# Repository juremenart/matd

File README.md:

# 8x8 Acoustic levitator

Videos of prototype (2 x 8x8 boards with standing wave, done with data from this repo):

https://www.youtube.com/shorts/MVx3mwE5fvo

https://www.youtube.com/shorts/kOz_UAl6hNY

Levitation of 4 particles:

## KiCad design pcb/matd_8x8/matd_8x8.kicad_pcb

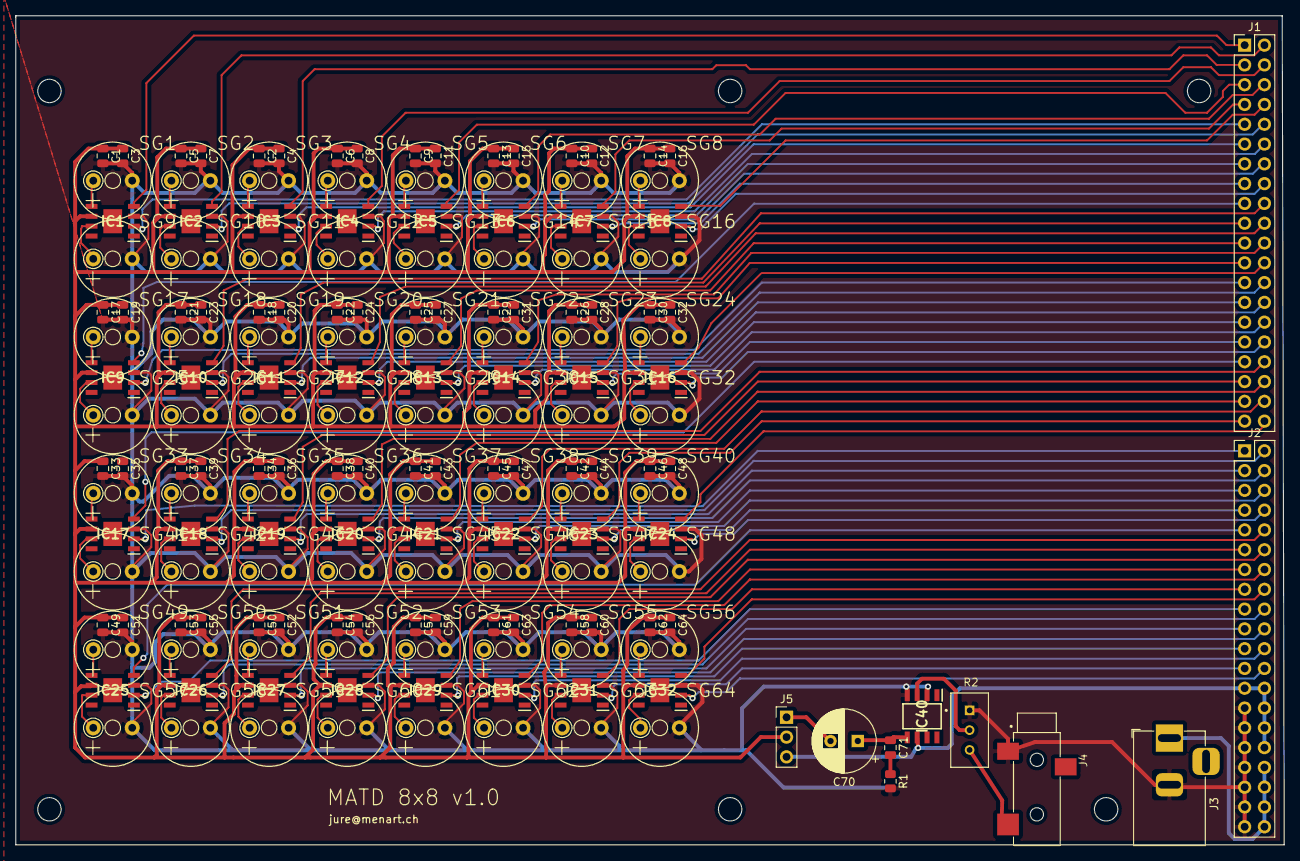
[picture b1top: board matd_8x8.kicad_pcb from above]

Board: 2 copper layers, 162.8 x 106.4 mm, 170 parts (0 on the bottom side), 137 nets.

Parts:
C1, C3, C5, C7, C9, C11, C13, C15, C17, C19, C21, C23, C25, C27, C29, C31, C33, C35, C37, C39, C41, C43, C45, C47, C49, C51, C53, C55, C57, C59, C61, C63: 4u7F; C_0805_2012Metric
C2, C4, C6, C8, C10, C12, C14, C16, C18, C20, C22, C24, C26, C28, C30, C32, C34, C36, C38, C40, C42, C44, C46, C48, C50, C52, C54, C56, C58, C60, C62, C64: 0u1F; C_0805_2012Metric
C70: 270uF; CP_Radial_D8.0mm_P3.50mm
C71: 0.05uF; C_0805_2012Metric
IC1, IC2, IC3, IC4, IC5, IC6, IC7, IC8, IC9, IC10, IC11, IC12, IC13, IC14, IC15, IC16, IC17, IC18, IC19, IC20, IC21, IC22, IC23, IC24, IC25, IC26, IC27, IC28, IC29, IC30, IC31, IC32: TC4427AEOA; SOIC127P602X168-9N
IC40: LM386M-1_NOPB; SOIC127P600X175-8N
J1, J2: Conn_02x20_Odd_Even; PinHeader_2x20_P2.54mm_Vertical
J3: Barrel_Jack; BarrelJack_Horizontal
J4: SJ-3523-SMT-TR; CUI_SJ-3523-SMT-TR
J5: Conn_01x03_Male; PinHeader_1x03_P2.54mm_Vertical
R1: 10; R_0805_2012Metric
R2: 3296W-1-103LF; TRIM_3296W-1-103LF
SG1, SG2, SG3, SG4, SG5, SG6, SG7, SG8, SG9, SG10, SG11, SG12, SG13, SG14, SG15, SG16, SG17, SG18, SG19, SG20, SG21, SG22, SG23, SG24, SG25, SG26, SG27, SG28, SG29, SG30, SG31, SG32, SG33, SG34, SG35, SG36, SG37, SG38, SG39, SG40, SG41, SG42, SG43, SG44, SG45, SG46, SG47, SG48, SG49, SG50, SG51, SG52, SG53, SG54, SG55, SG56, SG57, SG58, SG59, SG60, SG61, SG62, SG63, SG64: BMT1205XH7.5

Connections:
/SG1_SG16/SG1_IN: IC1.4, J1.1
/SG1_SG16/SG2_IN: IC2.4, J1.2
/SG1_SG16/SG3_IN: IC3.4, J1.3
/SG1_SG16/SG4_IN: IC4.4, J1.4
/SG1_SG16/SG5_IN: IC5.4, J1.5
/SG1_SG16/SG6_IN: IC6.4, J1.6
/SG1_SG16/SG7_IN: IC7.4, J1.7
/SG1_SG16/SG8_IN: IC8.4, J1.8
/SG1_SG16/SG9_IN: IC1.2, J1.9
/SG1_SG16/SG10_IN: IC2.2, J1.10
/SG1_SG16/SG11_IN: IC3.2, J1.11
/SG1_SG16/SG12_IN: IC4.2, J1.12
/SG1_SG16/SG13_IN: IC5.2, J1.13
/SG1_SG16/SG14_IN: IC6.2, J1.14
/SG1_SG16/SG15_IN: IC7.2, J1.15
/SG1_SG16/SG16_IN: IC8.2, J1.16
/SG17_SG32/SG17_IN: IC9.4, J1.17
/SG17_SG32/SG18_IN: IC10.4, J1.18
/SG17_SG32/SG19_IN: IC11.4, J1.19
/SG17_SG32/SG20_IN: IC12.4, J1.20
/SG17_SG32/SG21_IN: IC13.4, J1.21
/SG17_SG32/SG22_IN: IC14.4, J1.22
/SG17_SG32/SG23_IN: IC15.4, J1.23
/SG17_SG32/SG24_IN: IC16.4, J1.24
/SG17_SG32/SG25_IN: IC9.2, J1.25
/SG17_SG32/SG26_IN: IC10.2, J1.26
/SG17_SG32/SG27_IN: IC11.2, J1.27
/SG17_SG32/SG28_IN: IC12.2, J1.28
/SG17_SG32/SG29_IN: IC13.2, J1.29
/SG17_SG32/SG30_IN: IC14.2, J1.30
/SG17_SG32/SG31_IN: IC15.2, J1.31
/SG17_SG32/SG32_IN: IC16.2, J1.32
/SG17_SG32/VCC: C1.1, C2.1, C3.1, C4.1, C5.1, C6.1, C7.1, C8.1, C9.1, C10.1, C11.1, C12.1, C13.1, C14.1, C15.1, C16.1, C17.1, C18.1, C19.1, C20.1, C21.1, C22.1, C23.1, C24.1, C25.1, C26.1, C27.1, C28.1, C29.1, C30.1, C31.1, C32.1, C33.1, C34.1, C35.1, C36.1, C37.1, C38.1, C39.1, C40.1, C41.1, C42.1, C43.1, C44.1, C45.1, C46.1, C47.1, C48.1, C49.1, C50.1, C51.1, C52.1, C53.1, C54.1, C55.1, C56.1, C57.1, C58.1, C59.1, C60.1, C61.1, C62.1, C63.1, C64.1, IC1.6, IC2.6, IC3.6, IC4.6, IC5.6, IC6.6, IC7.6, IC8.6, IC9.6, IC10.6, IC11.6, IC12.6, IC13.6, IC14.6, IC15.6, IC16.6, IC17.6, IC18.6, IC19.6, IC20.6, IC21.6, IC22.6, IC23.6, IC24.6, IC25.6, IC26.6, IC27.6, IC28.6, IC29.6, IC30.6, IC31.6, IC32.6, J5.2
/SG33_SG48/SG33_IN: IC17.4, J1.33
/SG33_SG48/SG34_IN: IC18.4, J1.34
/SG33_SG48/SG35_IN: IC19.4, J1.35
/SG33_SG48/SG36_IN: IC20.4, J1.36
/SG33_SG48/SG37_IN: IC21.4, J1.37
/SG33_SG48/SG38_IN: IC22.4, J1.38
/SG33_SG48/SG39_IN: IC23.4, J1.39
/SG33_SG48/SG40_IN: IC24.4, J1.40
/SG33_SG48/SG41_IN: IC17.2, J2.1
/SG33_SG48/SG42_IN: IC18.2, J2.2
/SG33_SG48/SG43_IN: IC19.2, J2.3
/SG33_SG48/SG44_IN: IC20.2, J2.4
/SG33_SG48/SG45_IN: IC21.2, J2.5
/SG33_SG48/SG46_IN: IC22.2, J2.6
/SG33_SG48/SG47_IN: IC23.2, J2.7
/SG33_SG48/SG48_IN: IC24.2, J2.8
/SG49_SG64/SG49_IN: IC25.4, J2.9
/SG49_SG64/SG50_IN: IC26.4, J2.10
/SG49_SG64/SG51_IN: IC27.4, J2.11
/SG49_SG64/SG52_IN: IC28.4, J2.12
/SG49_SG64/SG53_IN: IC29.4, J2.13
/SG49_SG64/SG54_IN: IC30.4, J2.14
/SG49_SG64/SG55_IN: IC31.4, J2.15
/SG49_SG64/SG56_IN: IC32.4, J2.16
/SG49_SG64/SG57_IN: IC25.2, J2.17
/SG49_SG64/SG58_IN: IC26.2, J2.18
/SG49_SG64/SG59_IN: IC27.2, J2.19
/SG49_SG64/SG60_IN: IC28.2, J2.20
/SG49_SG64/SG61_IN: IC29.2, J2.21
/SG49_SG64/SG62_IN: IC30.2, J2.22
/SG49_SG64/SG63_IN: IC31.2, J2.23
/SG49_SG64/SG64_IN: IC32.2, J2.24
GND: C1.2, C2.2, C3.2, C4.2, C5.2, C6.2, C7.2, C8.2, C9.2, C10.2, C11.2, C12.2, C13.2, C14.2, C15.2, C16.2, C17.2, C18.2, C19.2, C20.2, C21.2, C22.2, C23.2, C24.2, C25.2, C26.2, C27.2, C28.2, C29.2, C30.2, C31.2, C32.2, C33.2, C34.2, C35.2, C36.2, C37.2, C38.2, C39.2, C40.2, C41.2, C42.2, C43.2, C44.2, C45.2, C46.2, C47.2, C48.2, C49.2, C50.2, C51.2, C52.2, C53.2, C54.2, C55.2, C56.2, C57.2, C58.2, C59.2, C60.2, C61.2, C62.2, C63.2, C64.2, IC1.3, IC2.3, IC3.3, IC4.3, IC5.3, IC6.3, IC7.3, IC8.3, IC9.3, IC10.3, IC11.3, IC12.3, IC13.3, IC14.3, IC15.3, IC16.3, IC17.3, IC18.3, IC19.3, IC20.3, IC21.3, IC22.3, IC23.3, IC24.3, IC25.3, IC26.3, IC27.3, IC28.3, IC29.3, IC30.3, IC31.3, IC32.3, IC40.2, IC40.4, J2.27, J2.29, J2.31, J2.33, J2.35, J2.37, J2.39, J3.2, J4.1, R1.2, R2.1, SG1.-, SG2.-, SG3.-, SG4.-, SG5.-, SG6.-, SG7.-, SG8.-, SG9.-, SG10.-, SG11.-, SG12.-, SG13.-, SG14.-, SG15.-, SG16.-, SG17.-, SG18.-, SG19.-, SG20.-, SG21.-, SG22.-, SG23.-, SG24.-, SG25.-, SG26.-, SG27.-, SG28.-, SG29.-, SG30.-, SG31.-, SG32.-, SG33.-, SG34.-, SG35.-, SG36.-, SG37.-, SG38.-, SG39.-, SG40.-, SG41.-, SG42.-, SG43.-, SG44.-, SG45.-, SG46.-, SG47.-, SG48.-, SG49.-, SG50.-, SG51.-, SG52.-, SG53.-, SG54.-, SG55.-, SG56.-, SG57.-, SG58.-, SG59.-, SG60.-, SG61.-, SG62.-, SG63.-, SG64.-
unnamed: C70.1, C71.1, IC40.5
unnamed: C70.2, J5.1
unnamed: C71.2, R1.1
unnamed: IC1.5, SG1.+
unnamed: IC1.7, SG9.+
unnamed: IC2.5, SG2.+
unnamed: IC2.7, SG10.+
unnamed: IC3.5, SG3.+
unnamed: IC3.7, SG11.+
unnamed: IC4.5, SG4.+
unnamed: IC4.7, SG12.+
unnamed: IC5.5, SG5.+
unnamed: IC5.7, SG13.+
unnamed: IC6.5, SG6.+
unnamed: IC6.7, SG14.+
unnamed: IC7.5, SG7.+
unnamed: IC7.7, SG15.+
unnamed: IC8.5, SG8.+
unnamed: IC8.7, SG16.+
unnamed: IC9.5, SG17.+
unnamed: IC9.7, SG25.+
unnamed: IC10.5, SG18.+
unnamed: IC10.7, SG26.+
unnamed: IC11.5, SG19.+
unnamed: IC11.7, SG27.+
unnamed: IC12.5, SG20.+
unnamed: IC12.7, SG28.+
unnamed: IC13.5, SG21.+
unnamed: IC13.7, SG29.+
unnamed: IC14.5, SG22.+
unnamed: IC14.7, SG30.+
unnamed: IC15.5, SG23.+
unnamed: IC15.7, SG31.+
unnamed: IC16.5, SG24.+
unnamed: IC16.7, SG32.+
unnamed: IC17.5, SG33.+
unnamed: IC17.7, SG41.+
unnamed: IC18.5, SG34.+
unnamed: IC18.7, SG42.+
unnamed: IC19.5, SG35.+
unnamed: IC19.7, SG43.+
unnamed: IC20.5, SG36.+
unnamed: IC20.7, SG44.+
unnamed: IC21.5, SG37.+
unnamed: IC21.7, SG45.+
unnamed: IC22.5, SG38.+
unnamed: IC22.7, SG46.+
unnamed: IC23.5, SG39.+
unnamed: IC23.7, SG47.+
unnamed: IC24.5, SG40.+
unnamed: IC24.7, SG48.+
unnamed: IC25.5, SG49.+
unnamed: IC25.7, SG57.+
unnamed: IC26.5, SG50.+
unnamed: IC26.7, SG58.+
unnamed: IC27.5, SG51.+
unnamed: IC27.7, SG59.+
unnamed: IC28.5, SG52.+
unnamed: IC28.7, SG60.+
unnamed: IC29.5, SG53.+
unnamed: IC29.7, SG61.+
unnamed: IC30.5, SG54.+
unnamed: IC30.7, SG62.+
unnamed: IC31.5, SG55.+
unnamed: IC31.7, SG63.+
unnamed: IC32.5, SG56.+
unnamed: IC32.7, SG64.+
unnamed: IC40.3, R2.2
unnamed: IC40.6, J2.25, J2.26, J2.28, J2.30, J2.32, J5.3
unnamed: J2.34, J2.36, J2.38, J2.40, J3.1
unnamed: J4.2, R2.3

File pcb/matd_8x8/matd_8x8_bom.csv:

"Id";"Designator";"Package";"Quantity";"Designation";"Supplier and ref";
1;"R2";"TRIM_3296W-1-103LF";1;"3296W-1-103LF";;;
2;"J4";"CUI_SJ-3523-SMT-TR";1;"SJ-3523-SMT-TR";;;
3;"IC40";"SOIC127P600X175-8N";1;"LM386M-1_NOPB";;;
4;"C70";"CP_Radial_D8.0mm_P3.50mm";1;"270uF";;;
5;"R1";"R_0805_2012Metric";1;"10";;;
6;"J5";"PinHeader_1x03_P2.54mm_Vertical";1;"Conn_01x03_Male";;;
7;"C71";"C_0805_2012Metric";1;"0.05uF";;;
8;"J2,J1";"PinHeader_2x20_P2.54mm_Vertical";2;"Conn_02x20_Odd_Even";;;
9;"SG64,SG63,SG62,SG61,SG60,SG59,SG58,SG57,SG56,SG55,SG54,SG53,SG52,SG51,SG50,SG49,SG48,SG47,SG46,SG45,SG44,SG43,SG42,SG41,SG40,SG39,SG38,SG37,SG36,SG35,SG34,SG33,SG32,SG31,SG30,SG29,SG28,SG27,SG26,SG25,SG24,SG23,SG22,SG21,SG20,SG19,SG18,SG17,SG16,SG15,SG14,SG13,SG12,SG11,SG10,SG9,SG8,SG7,SG6,SG5,SG4,SG3,SG2,SG1";"BMT1205XH7.5";64;"BMT1205XH7.5";;;
10;"J3";"BarrelJack_Horizontal";1;"Barrel_Jack";;;
11;"IC32,IC31,IC30,IC29,IC28,IC27,IC26,IC25,IC24,IC23,IC22,IC21,IC20,IC19,IC18,IC17,IC16,IC15,IC14,IC13,IC12,IC11,IC10,IC9,IC8,IC7,IC6,IC5,IC4,IC3,IC2,IC1";"SOIC127P602X168-9N";32;"TC4427AEOA";;;
12;"C64,C62,C60,C58,C56,C54,C52,C50,C48,C46,C44,C42,C40,C38,C36,C34,C32,C30,C28,C26,C24,C22,C20,C18,C16,C14,C12,C10,C8,C6,C4,C2";"C_0805_2012Metric";32;"0u1F";;;
13;"C63,C61,C59,C57,C55,C53,C51,C49,C47,C45,C43,C41,C39,C37,C35,C33,C31,C29,C27,C25,C23,C21,C19,C17,C15,C13,C11,C9,C7,C5,C3,C1";"C_0805_2012Metric";32;"4u7F";;;
14;",,,,,";"MountingHole_3mm";6;"MountingHole_3mm";;;

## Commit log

2023-04-12 initial import
2023-04-12 adding some images
